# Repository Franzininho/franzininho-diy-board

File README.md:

# Placa Franzininho DIY

Para mais detalhes sobre o projeto, montagem e programação, acesse a [documentação](https://franzininho.gitbook.io/franzininho-docs/)

O projeto é open hardware e foi publicado em [CC-BY-SA-4.0](https://github.com/Franzininho/franzininho-diy-board/blob/main/LICENSE)

A Franzininho DIY está certificada na [OSHWA com UID BR000003](https://certification.oshwa.org/br000003.html)

Entenda mais sobre open hardware: [Open source hardware: Conheça a definição e as boas práticas](https://www.embarcados.com.br/open-hardware-definicao/)

# Características da Franzininho DIY

- Placa em face simples - Para facilitar a fabricação caseira;
- Componentes em PTH - Para montagem manual pois esse é um dos objetivos do projeto;
- Microcontrolador ATtiny85-20PU - Compatibilidade com Arduino
- 5 pinos I/O - Todos os pinos do microcontrolador disponíveis para o usuário
- LED de POWER - LED Verde para indicação da alimentação
- LED Amarelo de uso geral conectado a um pino de I/O D1
- Programação através da USB por Bootloader

# Projeto

O projeto da PCB foi desenvolvido originalmente no Eagle CAD. Para acompanhar o histórico do projeto acesse a [branch master](https://github.com/Franzininho/franzininho-diy-board/tree/master)

Todos as versões estão disponíveis nos [releases](https://github.com/Franzininho/franzininho-diy-board/releases)

A versão atual é a V2.2. Projeto no Kicad.

Para contribuições considerar a branch main. A branch master foi mantida apenas para histórico.

# Contribuição

## Sugestões e Bugs no hardware

Você dever reportar bugs ou sugestões através dá [área de Issues](https://github.com/Franzininho/franzininho-diy-board/issues) aqui no github.

Certifique-se de cumprir os seguintes critérios ao criar/enviar sua issue:

- Use um título claro e descritivo para identificar o problema/sugestão.
- Descreva as etapas exatas para reproduzir o problema em tantos detalhes quanto possível
- Mencione o local onde este problema foi encontrado e o que sua sugestão afetará

## Contribuição para melhorias no hardware

As contribuições da comunidade são sempre bem-vindas!

Esta seção destina-se a ajudar qualquer pessoa interessada em contribuir para este repositório.

Antes de contribuir, primeiro obtenha a aprovação dos mantenedores do repositório e da comunidade, levantando um problema do GitHub usando as diretrizes mencionadas na seção de sugestões.

Depois de obter aprovação, você precisará fazer os seguintes passos (estas instruções assumem que você é um usuário do GitHub).

- 1: fork esse repositório
- 2: Faça as alterações, commit e push para o fork
- 3: Envie o seu Pull Request

## Se tiver dúvidas entre em contato

contato@franzininho.com.br

## Siga as redes sociais e participe da comunidade

- [Site](https://franzininho.com.br/)
- [Facebook](https://goo.gl/1adfUv)
- [Instagram](https://goo.gl/PbgHqA)
- [Youtube](https://goo.gl/pJqHjC)
- [Comunidade no Facebook](https://goo.gl/fskViM)

## Exemplos de simulação no [Wokwi](https://wokwi.com/)

- [Franzininho Blink](https://wokwi.com/arduino/projects/301693553069785610)
- [Display de 7 segmentos e projeto de relógio](https://wokwi.com/arduino/projects/301738586036765194)
- [Exemplo de sensor analógico de temperatura](https://wokwi.com/arduino/projects/301751077214093834)
- [Projeto de sensor digital de umidade e temperatura](https://wokwi.com/arduino/projects/301745949656482317)
- [Projeto de controle servo motor](https://wokwi.com/arduino/projects/302291615188255242)
- [Projeto de contador de pulso externo](https://wokwi.com/arduino/projects/302199144424931848)

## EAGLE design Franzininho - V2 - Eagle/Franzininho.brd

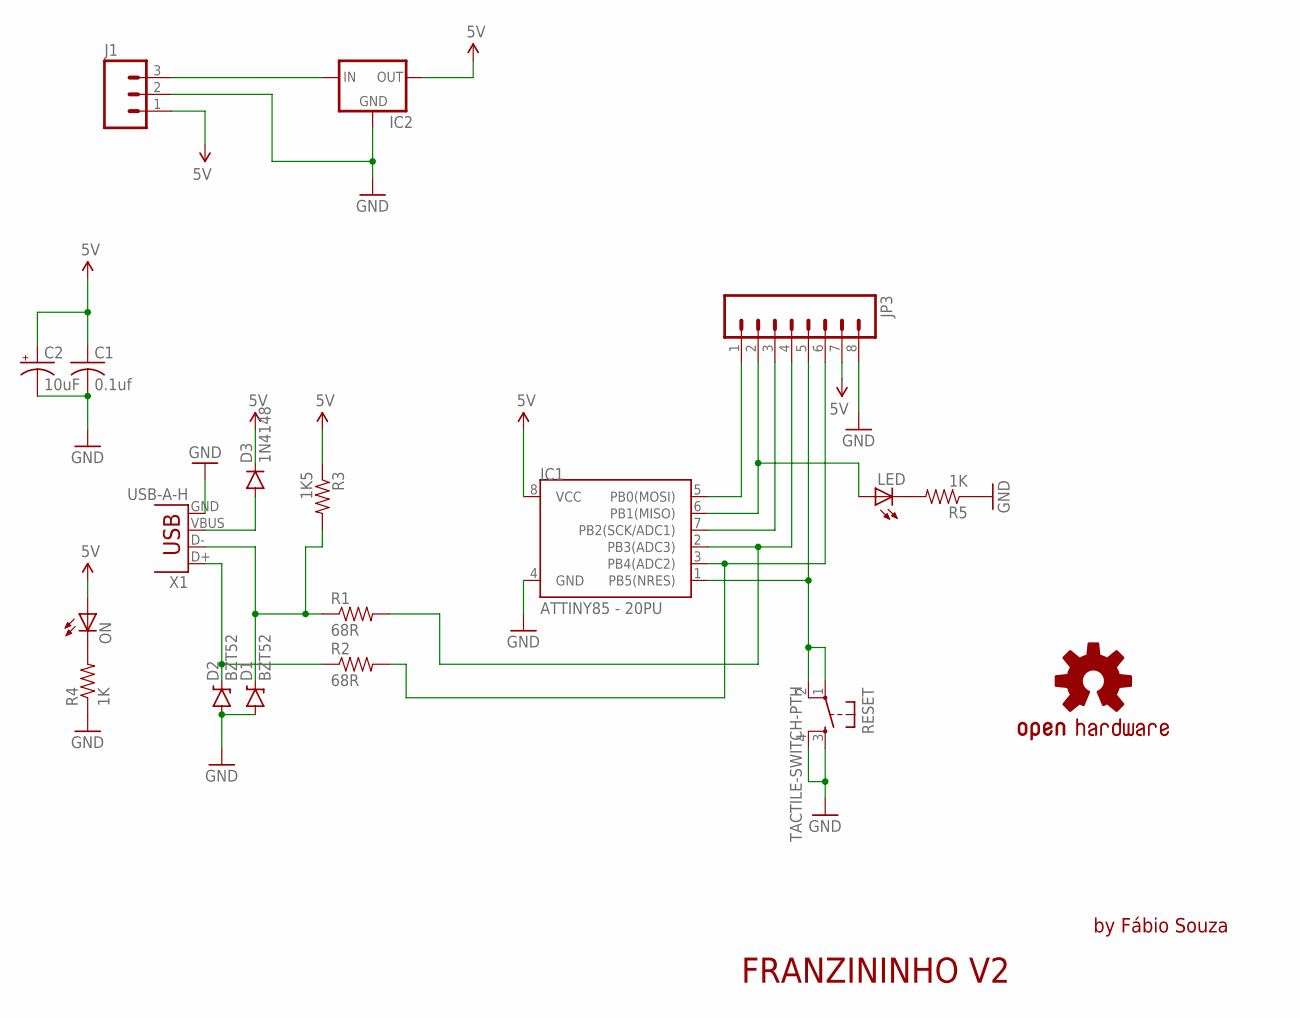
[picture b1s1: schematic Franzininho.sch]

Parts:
C1: 0.1uf; C025-025X050
C2: 10uF; E2,5-6E
D1, D2: BZT52; DIODE-BZT52
D3: 1N4148; DIODE-1N4148
IC1: ATTINY85 - 20PU; DIP08
IC2: 78LXX
J1: M03PTH; 1X03
JP3: M08; 1X08_ROUND
LED: LED3MM
LOGO1: OSHW-LOGOM; OSHW-LOGO-M
ON: LED3MM
R1, R2: 68R; AXIAL-0.4
R3: 1K5; AXIAL-0.4
R4, R5: 1K; AXIAL-0.4
RESET: TACTILE-SWITCH-PTH; TAC-SWITCH-PTH
X1: USB-A-H

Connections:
5V: C1.1, C2.+, D3.C, IC1.8 (VCC), IC2.OUT, J1.1, JP3.7, ON.A, R3.P$1 (1)
GND: C1.2, C2.-, D1.A, D2.A, IC1.4 (GND), IC2.GND, J1.2, JP3.8, R4.P$1 (1), R5.P$1 (1), RESET.3, RESET.4, X1.GND
unnamed: IC1.2 (PB3(ADC3)), JP3.4, R1.P$2 (2)
unnamed: IC1.6 (PB1(MISO)), JP3.2, LED.A
unnamed: IC1.5 (PB0(MOSI)), JP3.1
unnamed: D3.A, X1.VBUS
unnamed: IC1.7 (PB2(SCK/ADC1)), JP3.3
unnamed: IC1.3 (PB4(ADC2)), JP3.6, R2.P$2 (2)
unnamed: IC2.IN, J1.3
unnamed: IC1.1 (PB5(NRES)), JP3.5, RESET.1, RESET.2
unnamed: D1.C, R1.P$1 (1), R3.P$2 (2), X1.D-
unnamed: D2.C, R2.P$1 (1), X1.D+
unnamed: LED.K (C), R5.P$2 (2)
unnamed: ON.K (C), R4.P$2 (2)

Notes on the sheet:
FRANZININHO V2
by Fábio Souza

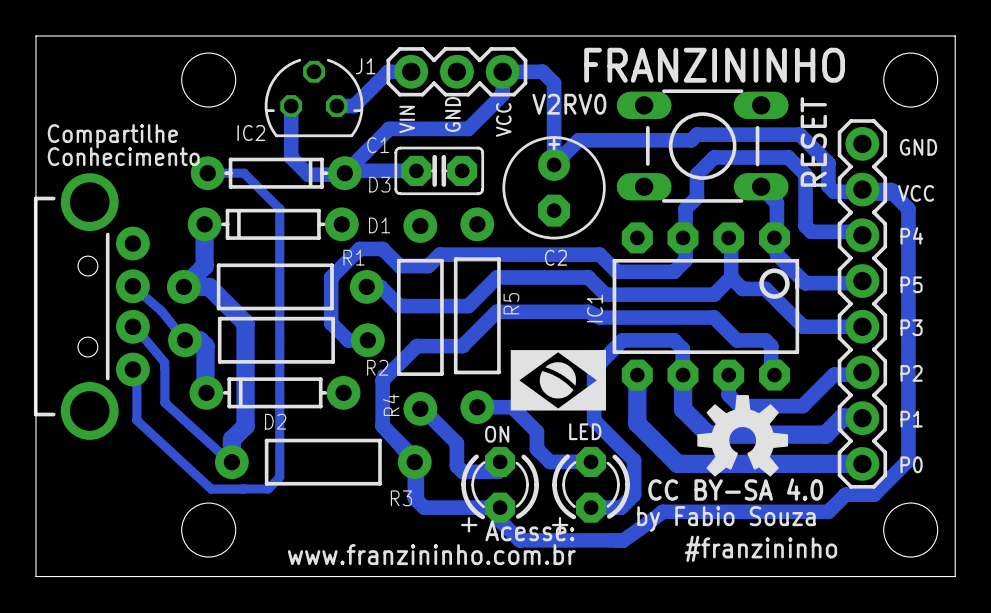
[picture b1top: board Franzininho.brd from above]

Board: 2 copper layers, 51.1 x 30.0 mm, 19 parts (0 on the bottom side), 14 nets.

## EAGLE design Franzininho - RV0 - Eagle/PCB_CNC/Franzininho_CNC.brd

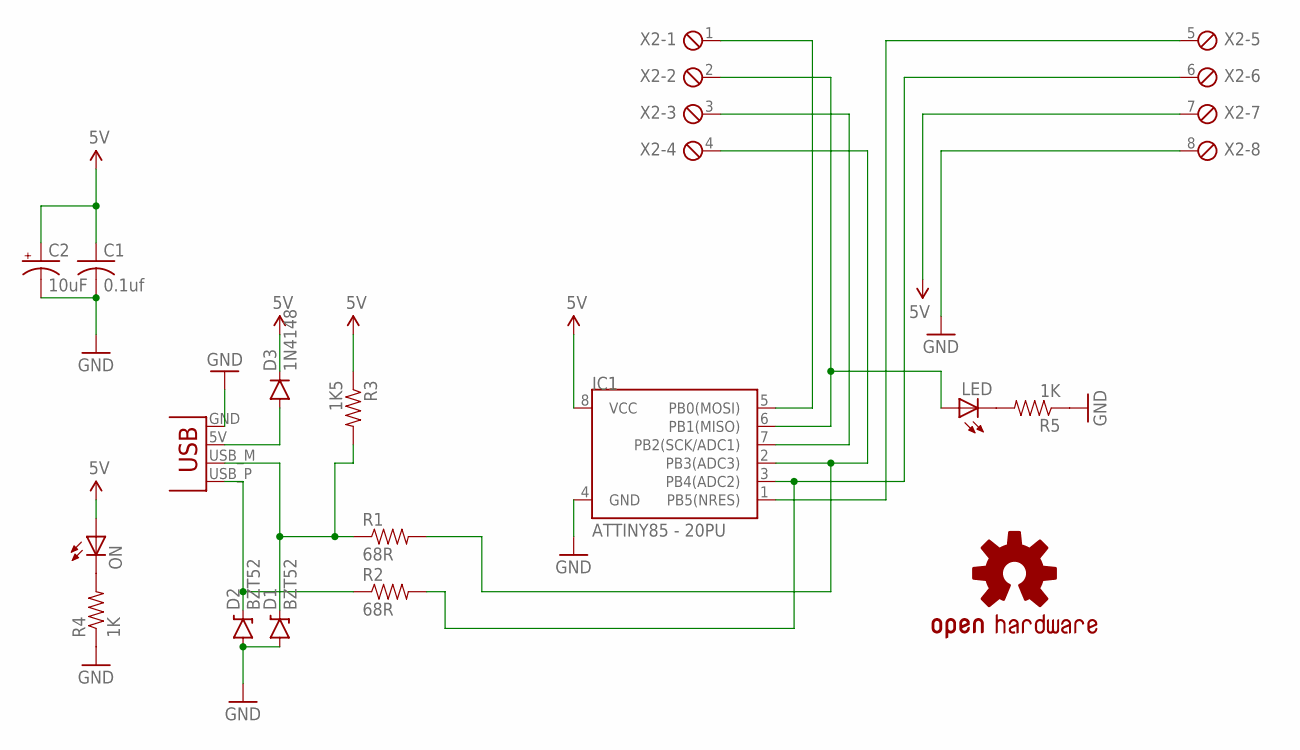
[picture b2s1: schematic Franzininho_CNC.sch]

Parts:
C1: 0.1uf; C025-025X050
C2: 10uF; E2,5-6E
D1, D2: BZT52; DIODE-BZT52
D3: 1N4148; DIODE-1N4148
IC1: ATTINY85 - 20PU; DIP08
LED: LED3MM
LOGO1: OSHW-LOGOL; OSHW-LOGO-L
ON: LED3MM
R1, R2: 68R; AXIAL-0.4
R3: 1K5; AXIAL-0.4
R4, R5: 1K; AXIAL-0.4
X1: USBPCB; USB-A-PCB
X2: MPT8; 8POL254

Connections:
5V: C1.1, C2.+, D3.C, IC1.8 (VCC), ON.A, R3.P$1 (1), X2.7
GND: C1.2, C2.-, D1.A, D2.A, IC1.4 (GND), R4.P$1 (1), R5.P$1 (1), X1.GND, X2.8
unnamed: IC1.2 (PB3(ADC3)), R1.P$2 (2), X2.4
unnamed: IC1.6 (PB1(MISO)), LED.A, X2.2
unnamed: IC1.5 (PB0(MOSI)), X2.1
unnamed: D3.A, X1.5V (VBUS)
unnamed: IC1.7 (PB2(SCK/ADC1)), X2.3
unnamed: IC1.3 (PB4(ADC2)), R2.P$2 (2), X2.6
unnamed: IC1.1 (PB5(NRES)), X2.5
unnamed: D1.C, R1.P$1 (1), R3.P$2 (2), X1.USB_M (D-)
unnamed: D2.C, R2.P$1 (1), X1.USB_P (D+)
unnamed: LED.K (C), R5.P$2 (2)
unnamed: ON.K (C), R4.P$2 (2)

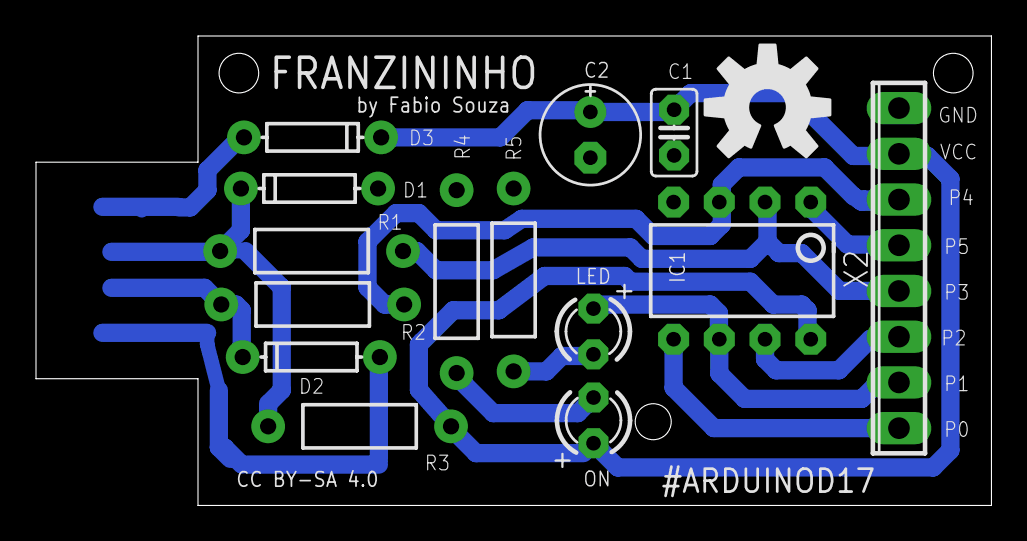
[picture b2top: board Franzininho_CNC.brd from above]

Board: 2 copper layers, 53.1 x 26.1 mm, 16 parts (1 on the bottom side), 13 nets.

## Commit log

2017-03-17 :octocat: Added .gitattributes & .gitignore files
2017-03-17 init
    Franzininho V0
2017-03-17 init
    organização de pastas
2017-03-17 resumo
2017-03-17 update
    aumentado um pouco o tamanho da placa
2017-03-18 nova dimensão
2017-03-19 CNC
    para usinagem em CNC*:
    Trilhas maiores, espaçamento menor
    *Usar essa versão apenas para usinagem em CNC
2017-03-19 layout
    Melhorias no Layout
    BOM
    Nova imagem da placa com melhor resolução e cotas
2017-03-22 nota
2017-03-23 Arquivos para preparação de produção em CNC
2017-03-24 tutorial fazedores
2017-03-27 gebers para produção
2017-03-27 atualização de arquivos
2017-04-04 updade de texto
2017-04-26 trilha para processo termico
2017-05-16 RV1
    Inserido botão de reset, furos, melhora no conector USB e aumentado um
    pouco as dimensões da placa.
2017-06-17 Exemplos
    Colocado mais exemplos
2017-06-17 bt
    atualizado exemplo de BT
2017-07-05 Upadate Readme
2017-07-06 imagens
    imagens para documentação
2017-07-10 add KiCAD version
2017-07-10 name
2017-07-10 link para texto das oficinas
2017-07-22 License
2017-08-04 V2
    Nova versão com regulador de tensão para alimentação externa
2017-08-04 V3
    placa com conector USB
2017-08-06 TickAttack and Franzininho
    This example shows how to control and manage Franzininho Robot using TickAttack (a task manager)
2017-08-27 imagens
2017-11-02 pastas
    Organização das pastas
2017-11-02 pinout
    Arquivos com pinout da Franzininho.
2017-11-02 imagens da placa
    Imagens da placa em diversas cores. Arquivos em SVG e PNG.
2017-11-02 placa branca
    Atualizada placa branca
2017-11-03 arquivos com trilhas na RV1
    Arquivos para fabricação caseira
2017-11-06 Furos transparentes
    Furos transparentes
2017-11-06 furos atualizados
    furos atualizados
2017-11-17 Tutorial Programação
    Primeiros passos para programação da Franzininho na IDE Arduino
2017-11-19 EmuladorTeclado
    Código para Emular teclado
2017-11-21 organizado as revisões
2017-11-22 organizando
2017-11-24 Fritzing part
    Componente para uso no Fritzing
2017-12-27 correção do conector USB
2018-02-13 tutorial import Fritzing
    Tutorial para importar componente Franzininho para o Fritizing
2018-02-13 Imagem no Readme
2018-02-13 imagem 4
2018-02-13 again
2018-02-13 ajustando imagem
2018-02-13 ajuste da imagem
2018-02-13 ajuste imagem
2018-02-13 todas as imagens
2018-02-13 ajuste de cabeçalhos
2018-02-13 mensagem
2018-02-15 sch e brd em pdf
    adiconado arquivos em pdf para facilitar o acesso a quem não tem CAD
2018-02-20 Enviado para organização
    Enviado para repositório Fritzing na organização Franzininho
2018-03-12 imagem componentes
2018-05-25 Organização das pasta e versões
2018-05-26 update git ignore
2018-05-26 Ajuste do readme
    Foi incluido os detalhes do projeto e como contribuir
2018-05-26 atualizado Readme
2018-05-26 link para a licença
2018-08-20 imagem esquemático
2018-09-30 correção e link
2018-09-30 link documentação
2018-10-21 Correção no README.md
2018-11-05 Compatibilidade Multiplataforma (Kicad Rev1) - Issue #21
2018-12-03 V2RV1
    Nova revisão da placa Franzininho V2. Foram feitos alguns ajustes no silk e footprints
2019-08-29 V2RV1 kicad
2019-08-29 V2RV2 - Corrigido GND no C2
2019-08-29 V2RV2 - gerber
2020-09-15 Improved production time
    Improved copper filled zones
    Improved some tracks
    Migrated to last version of KiCad
2020-11-27 Adiconando projeto Kicad da V2.2
2020-11-27 Removendo RV0 da branch main
2020-11-27 Removendo RV1 da branch main
2020-11-27 Removendo RV2 - Eagle da branch main
2020-11-27 Removendo V2 - Eagle da branch main
2020-11-27 Removendo V2RV1 -Kicad da branch main
2020-11-27 Removendo zip do gerber da v2rv1 da pasta
2020-11-27 Renomeando pasta do projeto Kicad para Franzininho DIY
2020-11-27 Renomeando arquivo .gitattributes
2020-11-27 Removendo arquivo .gitignore
2020-11-27 Adiconando arquivos que não estavam sendo monitorados devido ao .gitignore
2020-11-27 Ajustando o README.md para melhor apresentação após a limpeza no repositório e colocando a branch main como default
2021-02-06 Ajustando lib 3D e gerando arquivo step
2021-02-06 Adicionando informações sobre a certificação OSHWA
2021-02-06 Salvando arquivo de bkp
2021-02-06 Ajustando tamanho da imagem da licença OSHWA
2021-06-28 Update README.md
    Por favor, elimine os erros ortográficos
    Obrigada
2021-06-30 Ajuste de texto
2021-07-14 Ajuste da área de cobre para de solid para thermal relief para facilitar a soldagem. Ajuste de silks. Adicionado um ponto para indicar o pino 1 do mcu. Refeito área de cobre com um clearece menor
2021-07-24 Adicionando esquemático

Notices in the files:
parts and their libraries:
SparkFun: Licensing: CC v3.0 Share-Alike You are welcome to use this library for commercial purposes.
SparkFun-DigitalIC: Licensing: Creative Commons ShareAlike 4.0 International - https://creativecommons.org/licenses/by-sa/4.0
